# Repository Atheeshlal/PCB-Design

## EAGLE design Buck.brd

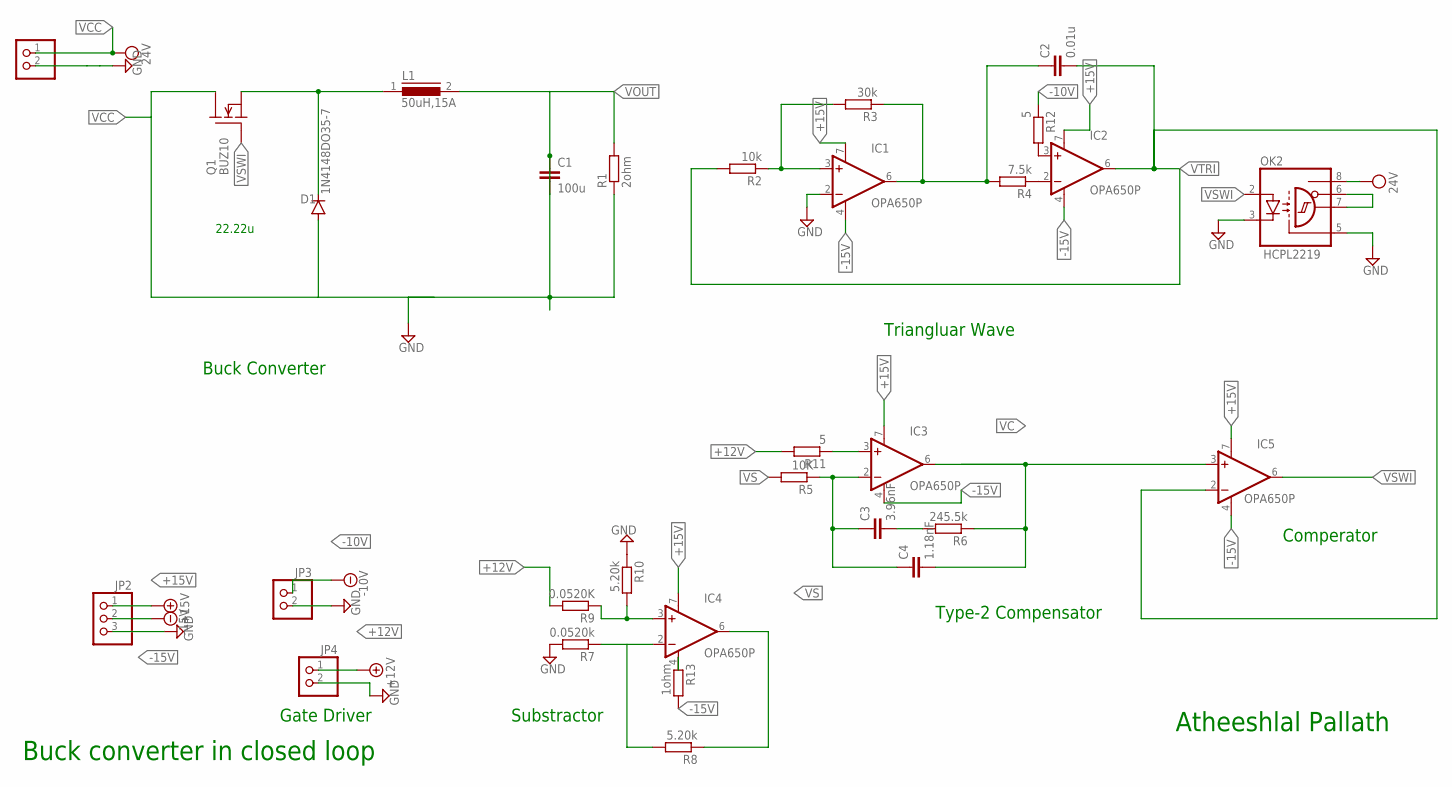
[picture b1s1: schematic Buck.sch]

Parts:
C1: 100u; C050-050X075
C2: 0.01u; C050-050X075
C3: 3.96nF; C050-050X075
C4: 1.18nF; C050-050X075
D1: 1N4148DO35-7; DO35-7
IC1, IC2, IC3, IC4, IC5: OPA650P; DIL08
JP1, JP3, JP4: PINHD-1X2; 1X02
JP2: PINHD-1X3; 1X03
L1: 50uH,15A; DR1,5A
OK2: HCPL2219; DIL08
Q1: BUZ10; TO220
R1: 2ohm; 0414/15
R2: 10k; 0414/15
R3: 30k; 0414/15
R4: 7.5k; 0414/15
R5: 10K; 0414/15
R6: 245.5k; 0414/15
R7: 0.0520k; 0414/15
R8, R10: 5.20k; 0414/15
R9: 0.0520K; 0414/15
R11, R12: 5; 0414/15
R13: 1ohm; 0414/15

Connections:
+12V: JP4.1
+15V: JP2.1
-10V: JP3.1
-15V: JP2.2
GND: IC1.2 (-IN), JP1.2, JP2.3, JP3.2, JP4.2, OK2.3 (C), OK2.5 (GND), R7.2, R10.1
unnamed: D1.C, L1.1, Q1.3 (S)
unnamed: IC4.4 (V-), R13.1
unnamed: IC1.3 (+IN), R2.1, R3.2
unnamed: OK2.6 (VE), OK2.7 (VO)
unnamed: IC2.2 (-IN), R4.1
unnamed: C3.1, C4.1, IC3.2 (-IN), R5.1
unnamed: C3.2, R6.2
unnamed: C2.1, IC1.6 (OUT), R3.1, R4.2
unnamed: IC4.3 (+IN), R9.1, R10.2
unnamed: IC4.2 (-IN), R7.1, R8.2
unnamed: IC2.3 (+IN), R12.2
unnamed: IC3.3 (+IN), R11.1
VC: C4.2, IC3.6 (OUT), IC5.3 (+IN), R6.1
VCC: JP1.1, OK2.8 (VCC)
VOUT: C1.1, C1.2, D1.A, L1.2, Q1.2 (D), R1.1, R1.2
VS: IC4.6 (OUT), R8.1
VSWI: IC5.6 (OUT)
VTRI: C2.2, IC2.6 (OUT), IC5.2 (-IN), R2.2

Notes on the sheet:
Buck converter in closed loop
Triangluar Wave
Gate Driver
Type-2 Compensator
Substractor
22.22u
Buck Converter
Comperator
Atheeshlal Pallath

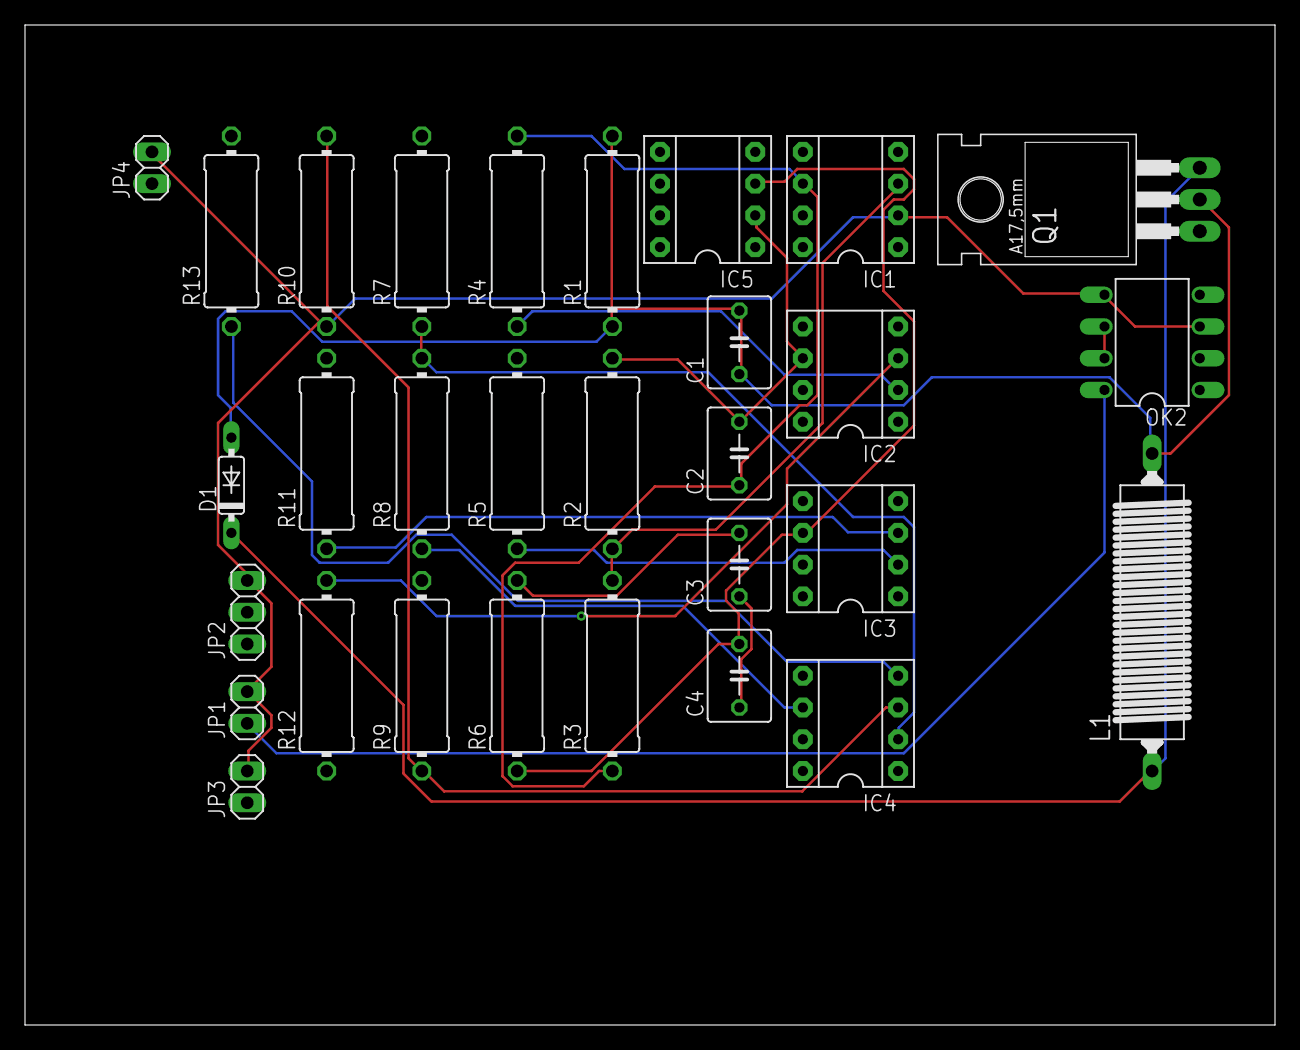
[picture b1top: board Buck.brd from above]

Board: 2 copper layers, 100.0 x 80.0 mm, 30 parts (0 on the bottom side), 18 nets.
